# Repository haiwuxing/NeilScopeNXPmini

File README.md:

# Neil Scope 3 NXP mini

# Описание

Плата для любительского осцилографа Neil Scope 3 для модификации с процессором NXP

### Оригинальный Neil Scope 3

[Страница проекта](http://hobby-research.at.ua/publ/razrabotki/izmerenija/neil_scope_3/4-1-0-42)

[Форум проекта](http://hobby-research.at.ua/forum/2-1-174)

### Модификация с процессором NXP

[Neil Scope 3. Глубокая модификация](https://radiokot.ru/artfiles/6446/)

[Обсуждение Neil Scope 3. Глубокая модификация](https://radiokot.ru/forum/viewtopic.php?f=25&t=158668)

### Поддерживаемые шилды дисплеев

[Дисплей 3,5 дюйма 240х400](https://ru.aliexpress.com/item/3-5-inch-TFT-LCD-Module-with-Touch-Panel-for-UNO-R3-Board-400-240-SD/32412795355.html)

[Дисплей 3,97 дюйма 240х400](https://ru.aliexpress.com/item/1-3-97-tft-st7793-uno-r3/32847715775.html)

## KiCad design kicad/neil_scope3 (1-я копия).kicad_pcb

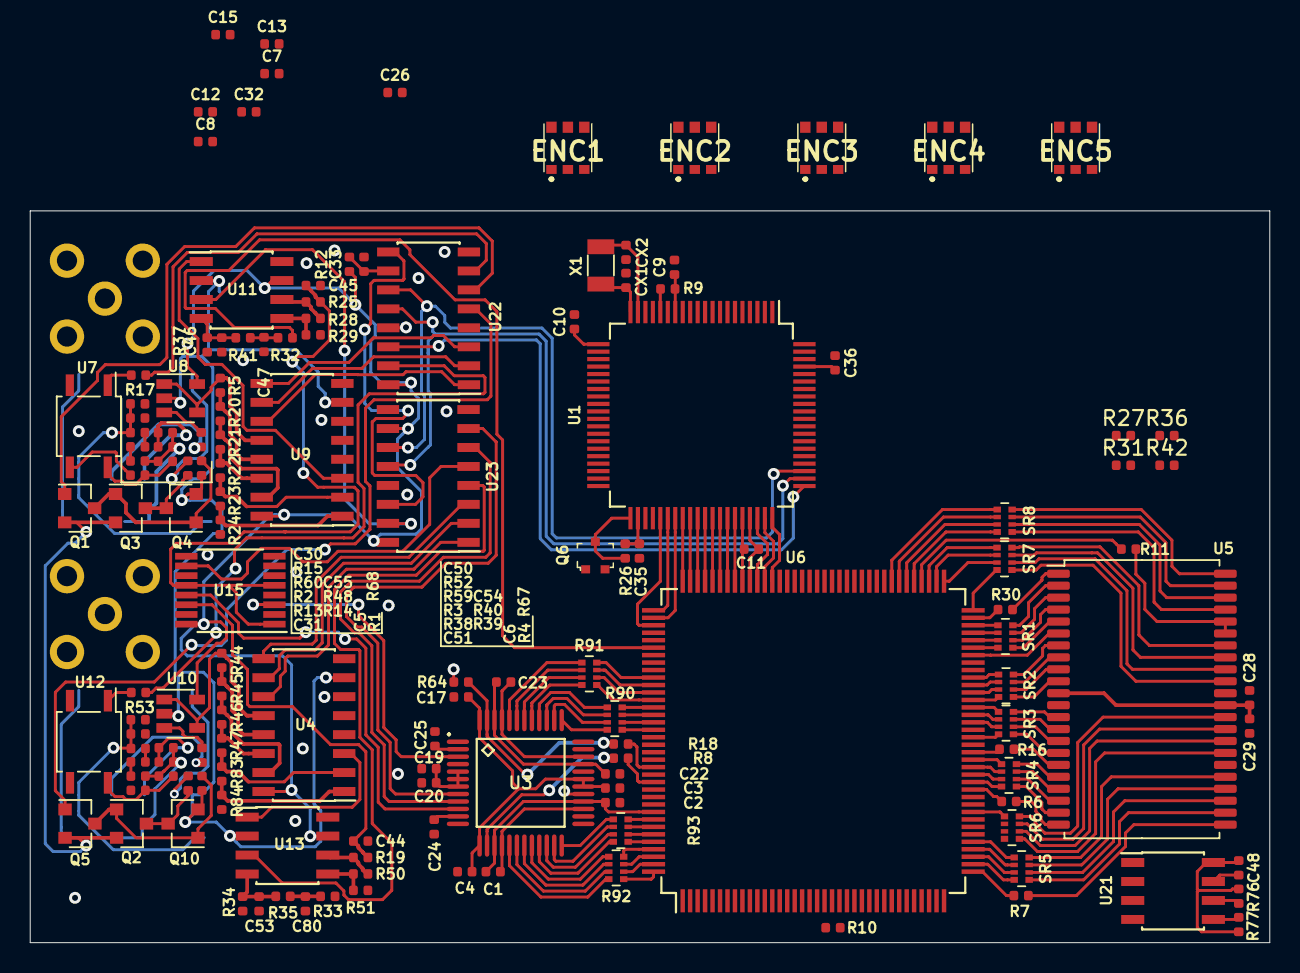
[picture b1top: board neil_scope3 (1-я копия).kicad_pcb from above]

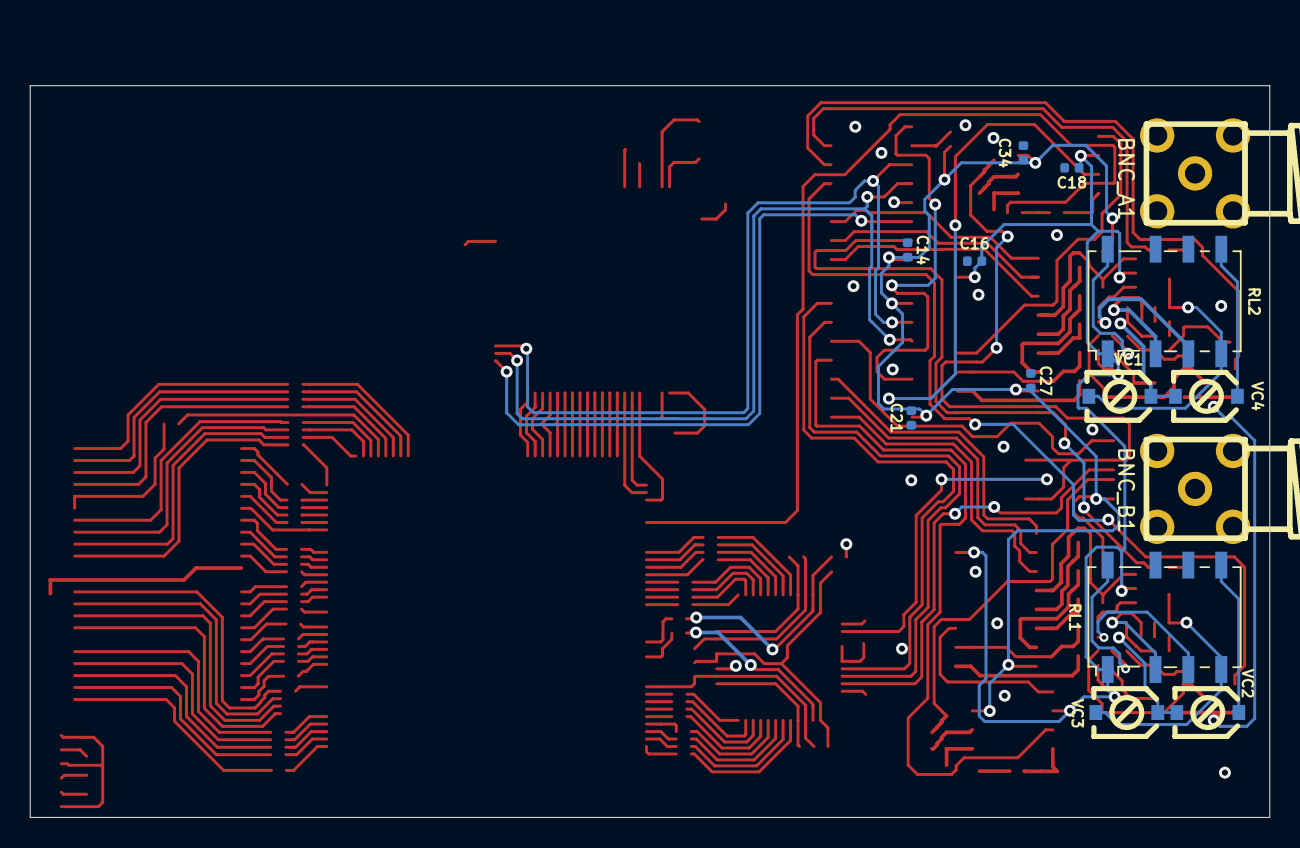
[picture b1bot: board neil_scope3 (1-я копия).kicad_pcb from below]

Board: 4 copper layers, 83.0 x 49.0 mm, 158 parts (14 on the bottom side), 220 nets.

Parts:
BNC_A1: BNCPTH; sma_90_r300.124.403
BNC_B1: BNCPTH; sma_90_r300.124.403
C1, C2, C3, C4, C7, C8, C9, C10, C11, C12, C13, C14, C15, C16, C17, C18, C20, C21, C22, C23, C24, C25, C26, C27, C28, C29, C32, C34, C35, C36, C48: 100nF; C_0402_1005Metric
C5, C6: 100uF; C_0402_1005Metric
C19, C47, C80: 10uF; C_0402_1005Metric
C30, C50: 2.2nF; C_0402_1005Metric
C31, C51: 100nF 50V; C_0402_1005Metric
C33: 2.2uF; C_0402_1005Metric
C44, C45: 160pF; C_0402_1005Metric
C46, C53: 1uF; C_0402_1005Metric
C54, C55: 150pF; C_0402_1005Metric
CX1, CX2: 20pF; C_0402_1005Metric
ENC1, ENC2, ENC3, ENC4, ENC5: SVM3A012A0A00R00
Q1, Q2, Q3, Q5: IRLML6401TRPBF; SOT-23
Q4, Q10: IRLML2502TRPBF; SOT-23
Q6: MMBT3904WT1G; SOT-323
R1, R4, R9, R26, R32, R33, R76, R77: 10k; R_0402_1005Metric
R2, R3, R13, R38, R59, R60: 330k 1%; R_0402_1005Metric
R5, R44: 499 1%; R_0402_1005Metric
R6, R7, R30: 22; R_0402_1005Metric
R8, R18: 10; R_0402_1005Metric
R10, R11, R16: 33; R_0402_1005Metric
R12: 100k; R_0402_1005Metric
R14, R39: 300; R_0402_1005Metric
R15, R52: 10k 1%; R_0402_1005Metric
R17, R27, R31, R36, R42, R53, R67, R68: 1k; R_0402_1005Metric
R19, R25: 39; R_0402_1005Metric
R20, R29, R45, R51: 300 1%; R_0402_1005Metric
R21, R46: 100 1%; R_0402_1005Metric
R22, R47: 49.9 1%; R_0402_1005Metric
R23, R83: 30 1%; R_0402_1005Metric
R24, R84: 20 1%; R_0402_1005Metric
R28, R50: 2.7k 1%; R_0402_1005Metric
R34, R37: 2.2k; R_0402_1005Metric
R35, R41: 18k; R_0402_1005Metric
R40, R48: 33k; R_0402_1005Metric
R64: NO; R_0402_1005Metric
R90, R91, R92, R93: 22; R_Array_Convex_4x0402
RL1, RL2: G6KU-2; Relay_DPDT_Omron_G6K-2F-Y
SR1, SR2, SR3, SR4, SR5, SR6, SR7, SR8: 22; R_Array_Convex_4x0402
U1: LPC175x; LQFP-80_12x12mm_P0.5mm
U3: AD9288BSTZ-100; QFP50P900X900X160-48
U4, U9: 74HC4051; SOIC-16_3.9x9.9mm_P1.27mm
U5: CY7C1041DV33-10ZSXI; TSOP-II-44_10.16x18.41mm_P0.8mm
U6: EPM570T144C5N; LQFP-144_20x20mm_P0.5mm
U7, U12: CPC1035NTR; SOP-4_3.8x4.1mm_P2.54mm
U8, U10: AD8065ART; SOT-23-5
U11, U13: AD8129; SOIC-8_3.9x4.9mm_P1.27mm
U15: 74HC4052SO; TSSOP-16_4.4x5mm_P0.65mm
U21: 24LC64; SOIC-8_3.9x4.9mm_P1.27mm
U22, U23: 74HC595; SOIC-16_3.9x9.9mm_P1.27mm
VC1, VC3: 10-30pF; MURATA-TZC3P
VC2, VC4: 2-10pF; MURATA-TZC3P
X1: 10MHz; Crystal_SMD_3215-2Pin_3.2x1.5mm

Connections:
0A: U9.11, U22.1
0B: U4.11, U23.1
1A: U9.10, U22.2
1B: U4.10, U23.2
2A: U9.9, U22.3
2B: U4.9, U23.3
+2.7V: C1.2, C2.2, C3.2, C4.2, C10.2, C11.1, C17.2, C22.2, C23.2, C28.2, C29.2, C35.1, C36.2, C48.2, Q1.2, Q2.2, Q3.2, Q5.2, R9.2, R26.1, R27.1, R31.1, R42.1, R76.2, R77.2, U1.8, U1.10, U1.16, U1.21, U1.34, U1.42, U1.56, U1.67, U1.77, U3.13, U3.15, U3.28, U3.30, U3.31, U3.33, U3.46, U3.48, U5.11, U5.33, U6.9, U6.19, U6.25, U6.46, U6.56, U6.64, U6.82, U6.90, U6.100, U6.116, U6.126, U6.136, U21.8
+3.3VA: C7.1, C12.1, C14.1, C15.1, C21.1, C27.1, C34.2, R12.2, U4.16, U8.5, U9.16, U10.5, U11.7, U13.7, U15.16, U22.16, U23.10, U23.16
-3.3VA: C8.1, C13.1, C16.2, C18.2, C26.1, C32.1, Q4.2, Q10.2, R1.1, R4.1, RL1.1, RL2.1, U4.7, U8.2, U9.7, U10.2, U11.2, U13.2
A0: R30.2, U6.71
A1: SR1.1, U6.70
A2: SR1.2, U6.69
A3: SR1.3, U6.68
A4: SR1.4, U6.67
A5: SR4.1, U6.52
A6: SR4.2, U6.51
A7: SR4.3, U6.50
A8: SR4.4, U6.49
A9: R6.2, U6.48
A10: R7.1, U6.37
A11: SR5.8, U6.38
A12: SR5.7, U6.39
A13: SR5.6, U6.40
A14: SR5.5, U6.41
A15: SR8.7, U6.78
A16: SR8.6, U6.79
A17: SR8.5, U6.80
ACLK: R18.2, U6.130
AD0: R90.5, U6.125
AD1: R90.6, U6.124
AD2: R90.7, U6.123
AD3: R90.8, U6.122
AD4: R91.5, U6.121
AD5: R91.6, U6.120
AD6: R91.7, U6.119
AD7: R91.8, U6.118
AD8: R93.8, U6.137
AD9: R93.7, U6.138
AD10: R93.6, U6.139
AD11: R93.5, U6.140
AD12: R92.8, U6.141
AD13: R92.7, U6.142
AD14: R92.6, U6.143
AD15: R92.5, U6.144
ADC_REFOUT_1.25V: C19.1, C20.1, U3.5, U3.6, U3.7
AGND: BNC_A1.2, BNC_B1.2, C3.1, C4.1, C14.2, C16.1, C17.1, C18.1, C19.2, C20.2, C21.2, C24.2, C25.2, C26.2, C27.2, C30.1, C32.2, C33.1, C34.1, C44.1, C45.1, C46.1, C47.1, C50.1, C53.1, C80.1, R15.1, R24.1, R29.1, R34.2, R37.2, R51.1, R52.1, R84.1, RL1.6, RL2.6, U3.1, U3.4, U3.12, U3.16, U3.45, U4.4, U4.5, U4.6, U4.8, U7.2, U9.4, U9.5, U9.6, U9.8, U11.8, U12.2, U13.8, U15.2, U15.4, U15.6, U15.7, U15.8, U15.9, U15.11, U15.15, U22.8, U22.13, U23.8, U23.13
AINA-: U3.3, U15.3
AINB-: U3.10, U15.13
BCLK: R8.2, U6.132
CE_S-: U5.6, U6.66
CLK_S: R11.1, U6.76
D0: SR2.1, U6.63
D1: SR2.2, U6.62
D2: SR2.3, U6.61
D3: SR2.4, U6.60
D4: SR3.1, U6.59
D5: SR3.2, U6.58
D6: SR3.3, U6.57
D7: SR3.4, U6.55
D8: SR6.8, U6.42
D9: SR6.7, U6.43
D10: SR6.6, U6.44
D11: SR6.5, U6.45
D12: SR7.8, U6.72
D13: SR7.7, U6.73
D14: SR7.6, U6.74
D15: SR7.5, U6.75
DGND: C1.1, C2.1, C9.2, C10.1, C11.2, C22.1, C23.1, C28.1, C29.1, C35.2, C36.1, C48.1, CX1.2, CX2.2, Q6.2, R36.1, U1.9, U1.12, U1.24, U1.33, U1.43, U1.57, U1.66, U1.78, U3.27, U3.29, U3.32, U3.34, U5.12, U5.34, U6.10, U6.17, U6.26, U6.47, U6.54, U6.65, U6.83, U6.92, U6.99, U6.115, U6.128, U6.135, U21.1, U21.2, U21.3, U21.4, U21.7
INTERL: U15.10, U23.5
unnamed: BNC_A1.1, C31.2, U7.3
unnamed: BNC_B1.1, C51.2, U12.3
unnamed: C5.2, Q3.3, Q4.3
unnamed: C6.2, Q2.3, Q10.3
unnamed: C9.1, R9.1, U1.14
unnamed: C12.2, C13.2, C54.2, R38.2, R39.1, R40.2, VC2.2, VC3.1
unnamed: C7.2, C8.2, C15.2, C55.2, R13.2, R14.1, R48.2, VC1.1, VC4.2
unnamed: C24.1, U3.11
unnamed: C25.1, U3.2
unnamed: C30.2, R15.2, R60.1, RL2.4, VC1.2
unnamed: C31.1, R14.2, U7.4
unnamed: C33.2, R12.1, U22.10
unnamed: C44.2, R19.2, U15.14
unnamed: C45.2, R25.2, U15.1, U15.5, U15.12
unnamed: C46.2, R37.1, R41.2, U11.4
unnamed: C47.2, R32.2, R41.1
unnamed: C50.2, R52.2, R59.1, RL1.4, VC3.2
unnamed: C51.1, R39.2, U12.4
unnamed: C53.2, R34.1, R35.2, U13.4
unnamed: C54.1, R40.1, RL1.2
unnamed: C55.1, R48.1, RL2.2
unnamed: C80.2, R33.2, R35.1
unnamed: CX1.1, U1.20, X1.2
unnamed: CX2.1, U1.19, X1.1
unnamed: Q1.3, Q3.1, Q4.1, R1.2
unnamed: Q6.3, R26.2, U1.41
unnamed: Q2.1, Q5.3, Q10.1, R4.2
unnamed: R2.1, R60.2
unnamed: R3.1, R59.2
unnamed: R3.2, R38.1
unnamed: R5.2, U8.1, U8.4, U9.12
unnamed: R6.1, U5.22
unnamed: R7.2, U5.23
unnamed: R10.1, U6.20
unnamed: R11.2, U5.39, U5.40
unnamed: R2.2, R13.1
unnamed: R16.1, U5.17
unnamed: R17.2, U7.1
unnamed: R18.1, R64.2, U3.47
unnamed: R19.1, R50.2, U13.6
unnamed: R20.1, R21.2, U9.15
unnamed: R5.1, R20.2, U9.13
unnamed: R21.1, R22.2, U9.14
unnamed: R22.1, R23.2, U9.2
unnamed: R23.1, R24.2, U9.1
unnamed: R25.1, R28.2, U11.6
unnamed: R28.1, R29.2, U11.5
unnamed: R30.1, U5.1
unnamed: R44.1, R45.2, U4.13
unnamed: R44.2, U4.12, U10.1, U10.4
unnamed: R45.1, R46.2, U4.15
unnamed: R46.1, R47.2, U4.14
unnamed: R47.1, R83.2, U4.2
unnamed: R50.1, R51.2, U13.5
unnamed: R53.2, U12.1
unnamed: R8.1, R64.1, U3.14
unnamed: R67.1, U10.3
unnamed: R67.2, RL1.3
unnamed: R68.1, U8.3
unnamed: R68.2, RL2.3
unnamed: R83.1, R84.2, U4.1
unnamed: R90.1, U3.40
unnamed: R90.2, U3.39
unnamed: R90.3, U3.38
unnamed: R90.4, U3.37
unnamed: R91.1, U3.44
unnamed: R91.2, U3.43
unnamed: R91.3, U3.42
unnamed: R91.4, U3.41
unnamed: R92.1, U3.20
unnamed: R92.2, U3.19
unnamed: R92.3, U3.18
unnamed: R92.4, U3.17
unnamed: R93.1, U3.24
unnamed: R93.2, U3.23
unnamed: R93.3, U3.22
unnamed: R93.4, U3.21
unnamed: RL1.5, VC2.1
unnamed: RL2.5, VC4.1
unnamed: SR1.5, U5.5
unnamed: SR1.6, U5.4
unnamed: SR1.7, U5.3
unnamed: SR1.8, U5.2
unnamed: SR2.5, U5.10
unnamed: SR2.6, U5.9
unnamed: SR2.7, U5.8
unnamed: SR2.8, U5.7
unnamed: SR3.5, U5.16
unnamed: SR3.6, U5.15
unnamed: SR3.7, U5.14
unnamed: SR3.8, U5.13
unnamed: SR4.5, U5.21
unnamed: SR4.6, U5.20
unnamed: SR4.7, U5.19
unnamed: SR4.8, U5.18
unnamed: SR5.1, U5.24
unnamed: SR5.2, U5.25
unnamed: SR5.3, U5.26
unnamed: SR5.4, U5.27
unnamed: SR6.1, U5.29
unnamed: SR6.2, U5.30
unnamed: SR6.3, U5.31
unnamed: SR6.4, U5.32
unnamed: SR7.1, U5.35
unnamed: SR7.2, U5.36
unnamed: SR7.3, U5.37
unnamed: SR7.4, U5.38
unnamed: SR8.2, U5.42
unnamed: SR8.3, U5.43
unnamed: SR8.4, U5.44
unnamed: U9.3, U11.1
unnamed: U4.3, U13.1
unnamed: U22.9, U23.14
OCA: R17.1, U22.7
OCB: R53.1, U22.15
OE_S-: SR8.8, U6.77
O_E: SR8.1, U5.41
PDN_A-: U11.3, U23.15
PDN_B-: U13.3, U23.4
PWMA: U1.60, U6.96
PWMB: U1.59, U6.97
PWM_A: R32.1, U6.114
PWM_B: R33.1, U6.1
Q0: U1.58, U6.98
Q1: U1.55, U6.101
Q2: U1.54, U6.102
Q3: U1.53, U6.103
Q4: U1.52, U6.104
Q5: U1.51, U6.105
Q6: U1.50, U6.106
Q7: U1.49, U6.107
RD: U1.48, U6.108
RL_A0: C5.1, RL2.8
RL_B0: C6.1, RL1.8
RL_CA: Q1.1, U22.6
RL_CB: Q5.1, U22.5
RS: U1.46, U6.109
S1: U3.8, U23.7
S2: U3.9, U23.6
SCL: R76.1, U1.40, U21.6
SDA: R77.1, U1.39, U21.5
SPI_CS: U1.62, U22.12, U23.12
SPI_MOSI: U1.61, U22.14
SPI_SCK: U1.63, U22.11, U23.11
TCK: R36.2, U6.35
TDI: R31.2, U6.34
TDO: R42.2, U6.36
TMS: R27.2, U6.33
WE_S-: R16.2, U6.53
WR: U1.47, U6.110
WR_SRAM_RDY: U1.45, U6.111

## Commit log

2018-11-25 a msg
